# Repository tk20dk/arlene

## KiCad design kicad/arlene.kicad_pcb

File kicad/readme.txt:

0C  = 34.2K 14.6uA
10C = 20.0K 25.0uA
25C = 10.0K 50.0uA
60C =  2.5K 200.0uA

2.8V / 0.0002A = 14K

3.30V at 60C
1.20V at 25C
1.15V at 10C
1.00v at 0C

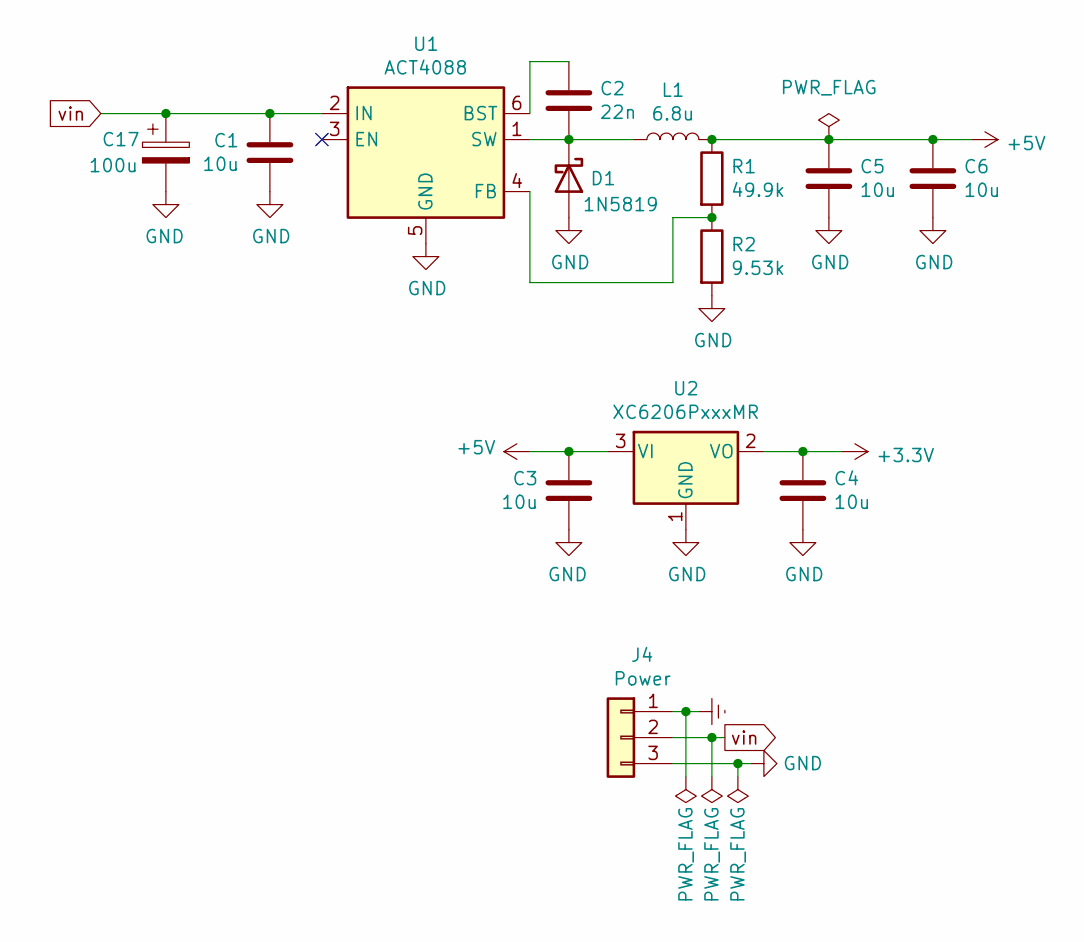
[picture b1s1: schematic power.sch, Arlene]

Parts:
C1, C3, C4, C5, C6: 10u; C_0805_2012Metric
C2: 22n; C_0603_1608Metric
C17: 100u; CP_EIA-7343-31_Kemet-D
D1: 1N5819; D_0805_2012Metric
J4: Power; JST_XH_B3B-XH-A_1x03_P2.50mm_Vertical
L1: 6.8u; L_4.1x4.1_H1.75
R1: 49.9k; R_0603_1608Metric
R2: 9.53k; R_0603_1608Metric
U1: ACT4088; SOT-23-6
U2: XC6206PxxxMR; SOT-23

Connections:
+5V: C3.1, C5.1, C6.1, L1.2, R1.1, U2.3 (VI); also elsewhere on the board
Earth: J4.1; also elsewhere on the board
GND: C1.2, C3.2, C4.2, C5.2, C6.2, C17.2, D1.2 (A), J4.3, R2.2, U1.5 (GND), U2.1 (GND); also elsewhere on the board
unnamed: C2.1, U1.6 (BST)
unnamed: C2.2, D1.1 (K), L1.1, U1.1 (SW)
unnamed: R1.2, R2.1, U1.4 (FB)
vin: C1.1, C17.1, J4.2, U1.2 (IN); also elsewhere on the board

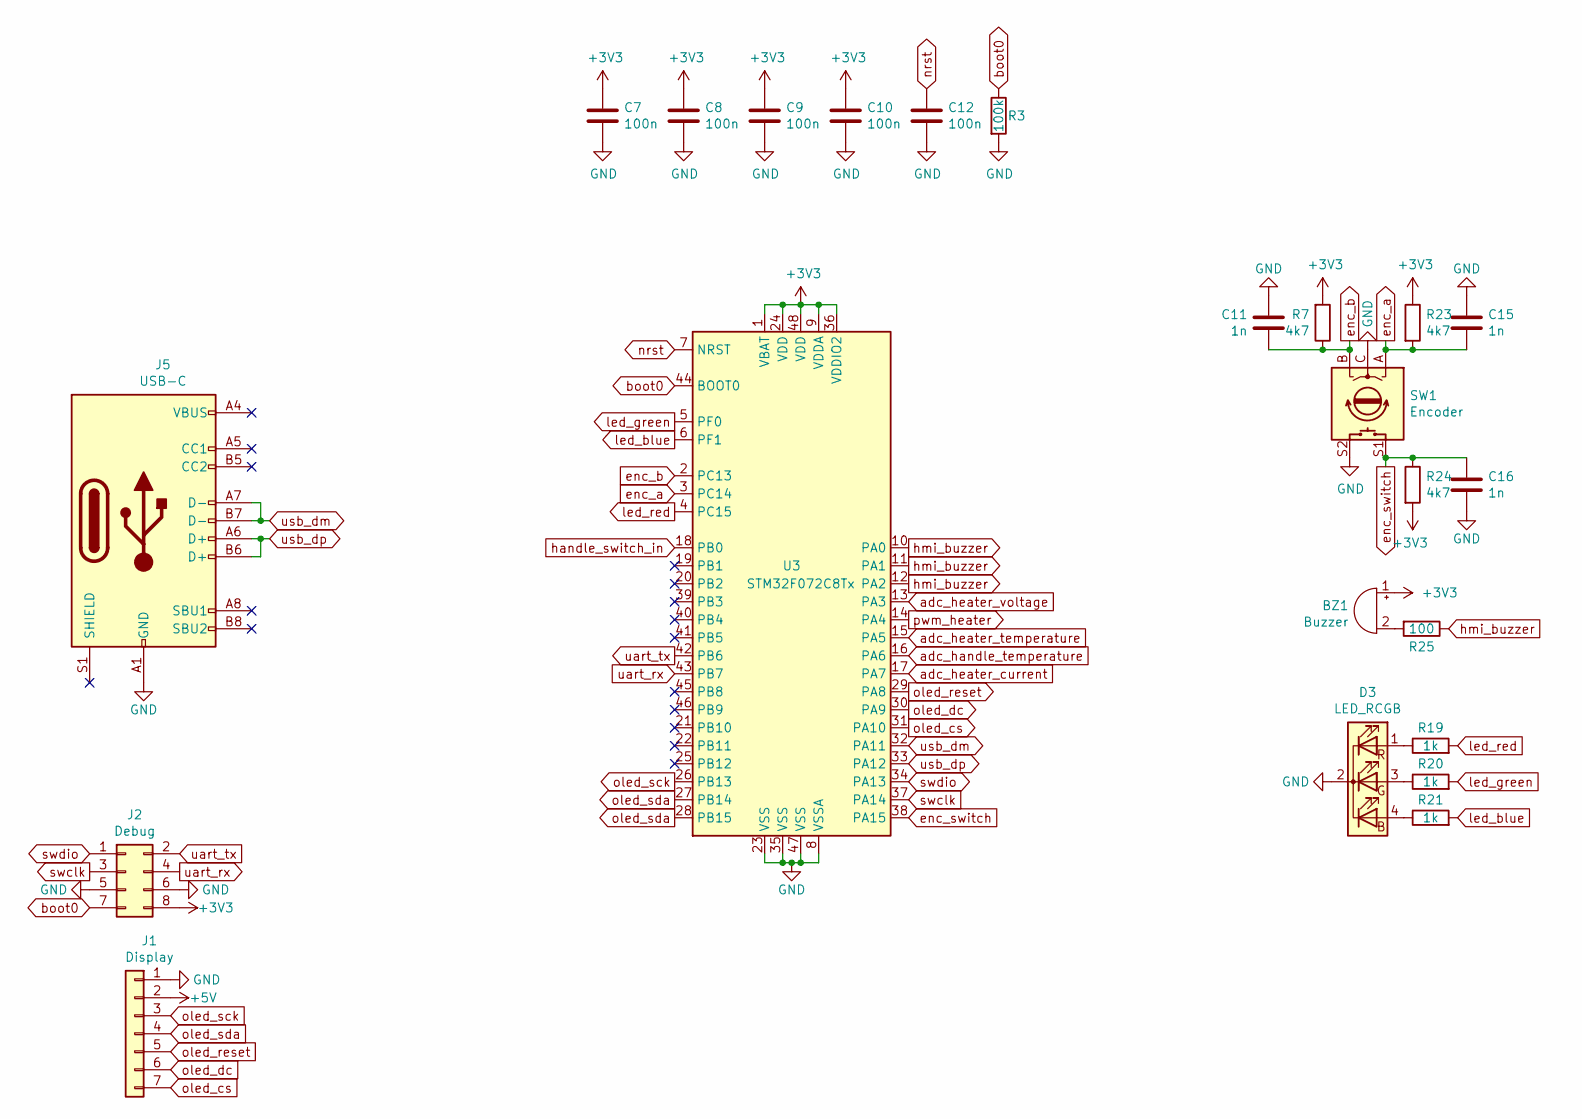
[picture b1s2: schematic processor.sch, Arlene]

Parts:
BZ1: Buzzer; Buzzer_12x9.5RM7.6
C7, C8, C9, C10, C12: 100n; C_0603_1608Metric
C11, C15, C16: 1n; C_0603_1608Metric
D3: LED_RCGB; LED_D5.0mm-4_RGB
J1: Display; PinHeader_1x07_P2.54mm_Vertical
J2: Debug; PinHeader_2x04_P2.54mm_Vertical
J5: USB-C; usb-c_14pin_tht_vertical
R3: 100k; R_0603_1608Metric
R7, R23, R24: 4k7; R_0603_1608Metric
R19, R20, R21: 1k; R_0603_1608Metric
R25: 100; R_0603_1608Metric
SW1: Encoder; RotaryEncoder_Alps_EC12E-Switch_Vertical_H20mm
U3: STM32F072C8Tx; LQFP-48_7x7mm_P0.5mm

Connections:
+5V: J1.2; also elsewhere on the board
GND: C7.2, C8.2, C9.2, C10.2, C11.2, C12.2, C15.1, C16.2, D3.2 (K), J1.1, J2.5, J2.6, J5.A1 (GND), J5.A12 (GND), J5.B1 (GND), J5.B12 (GND), R3.2, SW1.C, SW1.S2, U3.8 (VSSA), U3.23 (VSS), U3.35 (VSS), U3.47 (VSS); also elsewhere on the board
unnamed: BZ1.2 (+), R25.2
unnamed: D3.1 (RA), R19.1
unnamed: D3.3 (GA), R20.1
unnamed: D3.4 (BA), R21.1
unnamed: J5.A4 (VBUS), J5.A9 (VBUS), J5.B4 (VBUS), J5.B9 (VBUS)
adc_handle_temperature: U3.16 (PA6); also elsewhere on the board
adc_heater_current: U3.17 (PA7); also elsewhere on the board
adc_heater_temperature: U3.15 (PA5); also elsewhere on the board
adc_heater_voltage: U3.13 (PA3); also elsewhere on the board
boot0: J2.7, R3.1, U3.44 (BOOT0)
enc_a: C15.2, R23.2, SW1.A, U3.3 (PC14)
enc_b: C11.1, R7.1, SW1.B, U3.2 (PC13)
enc_switch: C16.1, R24.1, SW1.S1, U3.38 (PA15)
handle_switch_in: U3.18 (PB0); also elsewhere on the board
hmi_buzzer: R25.1, U3.10 (PA0), U3.11 (PA1), U3.12 (PA2)
led_blue: R21.2, U3.6 (PF1)
led_green: R20.2, U3.5 (PF0)
led_red: R19.2, U3.4 (PC15)
nrst: C12.1, U3.7 (NRST)
oled_cs: J1.7, U3.31 (PA10)
oled_dc: J1.6, U3.30 (PA9)
oled_reset: J1.5, U3.29 (PA8)
oled_sck: J1.3, U3.26 (PB13)
oled_sda: J1.4, U3.27 (PB14), U3.28 (PB15)
pwm_heater: U3.14 (PA4); also elsewhere on the board
swclk: J2.3, U3.37 (PA14)
swdio: J2.1, U3.34 (PA13)
uart_rx: J2.4, U3.43 (PB7)
uart_tx: J2.2, U3.42 (PB6)
usb_dm: J5.A7 (D-), J5.B7 (D-), U3.32 (PA11)
usb_dp: J5.A6 (D+), J5.B6 (D+), U3.33 (PA12)

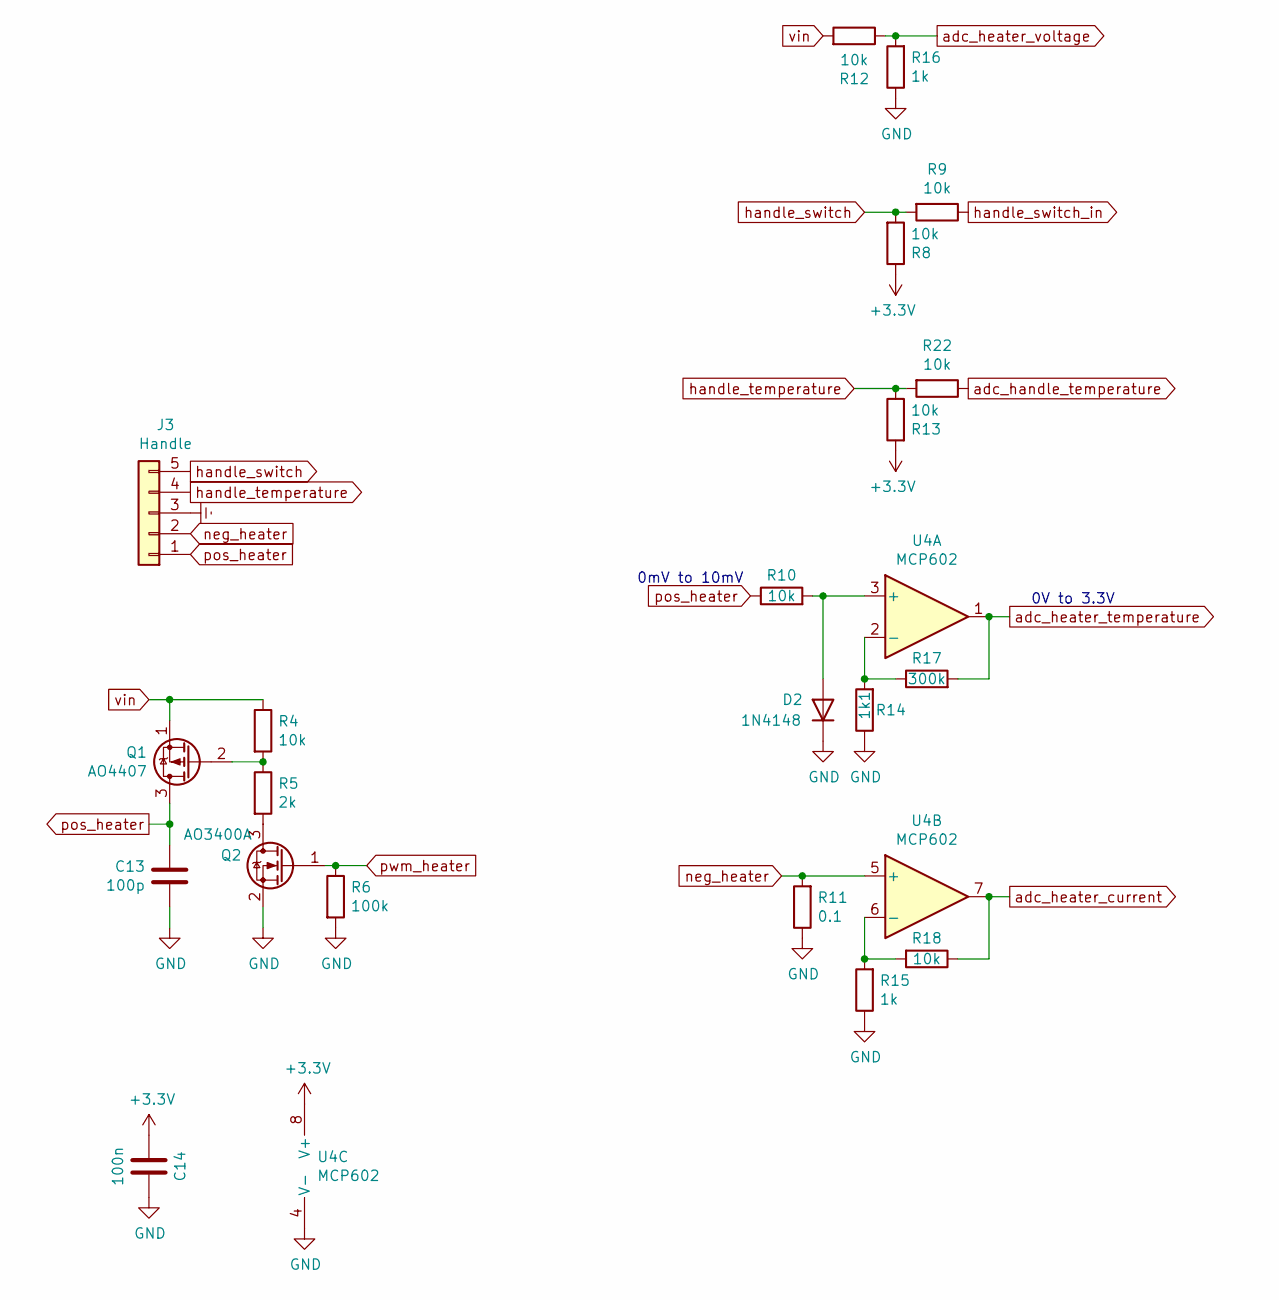
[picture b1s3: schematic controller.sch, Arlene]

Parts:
C13: 100p; C_0603_1608Metric
C14: 100n; C_0603_1608Metric
D2: 1N4148; D_SOD-323
J3: Handle; JST_XH_B5B-XH-A_1x05_P2.50mm_Vertical
Q1: AO4407; SOIC-8_PMOS_SGD_3.9x4.9mm_P1.27mm
Q2: AO3400A; SOT-23
R4, R8, R9, R10, R12, R13, R18, R22: 10k; R_0603_1608Metric
R5: 2k; R_0603_1608Metric
R6: 100k; R_0603_1608Metric
R11: 0.1; R_2512_6332Metric
R14: 1k1; R_0603_1608Metric
R15, R16: 1k; R_0603_1608Metric
R17: 300k; R_0603_1608Metric
U4: MCP602; SOIC-8_3.9x4.9mm_P1.27mm

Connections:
Earth: J3.3; also elsewhere on the board
GND: C13.2, C14.1, D2.1 (K), Q2.2 (S), R6.2, R11.1, R14.1, R15.1, R16.1, U4.4 (V-); also elsewhere on the board
unnamed: D2.2 (A), R10.2, U4.3 (+)
unnamed: Q1.2 (G), R4.2, R5.1
unnamed: Q2.3 (D), R5.2
unnamed: R14.2, R17.1, U4.2 (-)
unnamed: R15.2, R18.2, U4.6 (-)
adc_handle_temperature: R22.1; also elsewhere on the board
adc_heater_current: R18.1, U4.7; also elsewhere on the board
adc_heater_temperature: R17.2, U4.1; also elsewhere on the board
adc_heater_voltage: R12.1, R16.2; also elsewhere on the board
handle_switch: J3.5, R8.2, R9.2
handle_switch_in: R9.1; also elsewhere on the board
handle_temperature: J3.4, R13.1, R22.2
neg_heater: J3.2, R11.2, U4.5 (+)
pos_heater: C13.1, J3.1, Q1.3 (D), R10.1
pwm_heater: Q2.1 (G), R6.1; also elsewhere on the board
vin: Q1.1 (S), R4.1, R12.2; also elsewhere on the board

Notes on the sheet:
0V to 3.3V
0mV to 10mV

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
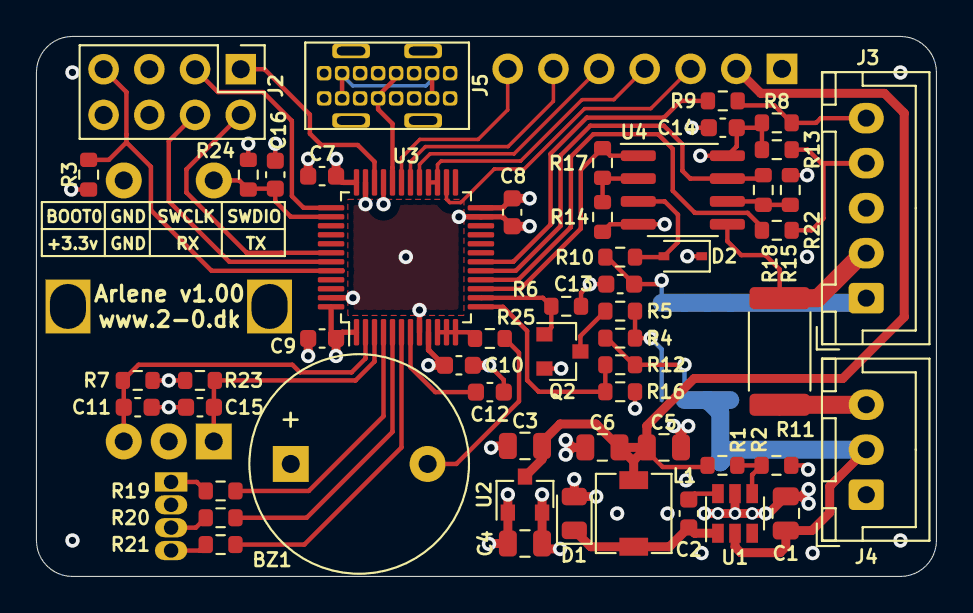
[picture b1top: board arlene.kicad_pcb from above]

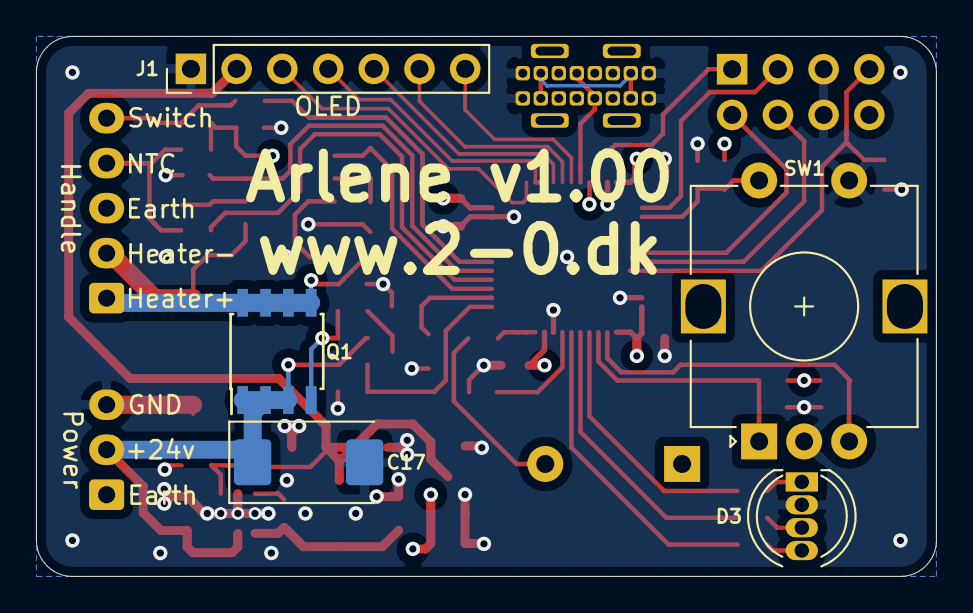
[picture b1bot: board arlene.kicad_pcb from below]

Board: 4 copper layers, 50.0 x 30.0 mm, 59 parts (5 on the bottom side), 48 nets.

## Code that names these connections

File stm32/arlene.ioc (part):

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PB13.GPIOParameters=GPIO_PuPd,GPIO_Label,GPIO_ModeDefaultEXTI
Mcu.UserName=STM32F072C8Tx
PB14.GPIO_Label=LED2_GREEN
PA11.Mode=Device
PA6.GPIO_Label=HMI_BUZZER
PB13.GPIO_Label=ENC_A
PB13.Signal=GPXTI13
PB15.Signal=GPIO_Output
RCC.SYSCLKSource=RCC_SYSCLKSOURCE_HSI48
PA15.GPIO_Label=LED1_RED
PB4.GPIOParameters=GPIO_Label
PA12.Signal=USB_DP
PB6.Signal=I2C1_SCL
PB6.Mode=I2C
PA8.GPIOParameters=GPIO_Label
PA4.GPIO_PuPd=GPIO_PULLUP
PB12.GPIO_Label=ENC_B
PA14.Mode=Serial_Wire
PA0.Mode=IN0
PB3.GPIOParameters=GPIO_Label
PB7.Signal=I2C1_SDA
PA8.Signal=GPIO_Output
PA0.Signal=ADC_IN0
Mcu.Package=LQFP48
PA6.Signal=GPIO_Output
PA10.Signal=USART1_RX
PA15.Signal=GPIO_Output
PA5.GPIOParameters=GPIO_Label
PB14.GPIOParameters=GPIO_Label
PA4.GPIO_Label=HANDLE_SWITCH
PB4.Signal=GPIO_Output
PA3.Signal=ADC_IN3
PB3.GPIO_Label=LED1_GREEN
PA6.GPIOParameters=GPIO_Label
PA15.GPIOParameters=GPIO_Label
PA10.Mode=Asynchronous
PA7.GPIO_ModeDefaultEXTI=GPIO_MODE_IT_FALLING
PB13.GPIO_ModeDefaultEXTI=GPIO_MODE_IT_FALLING
PA13.Signal=SYS_SWDIO
PA3.Mode=IN3
PA9.Mode=Asynchronous
PA8.GPIO_Label=LED2_BLUE
PA9.Signal=USART1_TX
PA4.GPIO_ModeDefaultEXTI=GPIO_MODE_IT_FALLING
PA1.Signal=ADC_IN1
PA7.GPIO_PuPd=GPIO_PULLUP
PB14.Signal=GPIO_Output
PA5.Signal=S_TIM2_CH1_ETR
board=custom
PB13.GPIO_PuPd=GPIO_PULLUP
PA1.Mode=IN1
PB4.GPIO_Label=LED1_BLUE
PB15.GPIO_Label=LED2_RED
PA4.GPIOParameters=GPIO_PuPd,GPIO_Label,GPIO_ModeDefaultEXTI
PB15.GPIOParameters=GPIO_Label
PA13.Mode=Serial_Wire
Mcu.Name=STM32F072C(8-B)Tx
PA2.Signal=ADC_IN2
PB3.Signal=GPIO_Output
PA4.Signal=GPXTI4
RCC.SYSCLKFreq_VALUE=48000000
PA7.GPIO_Label=ENC_SWITCH
PA12.Mode=Device
PA5.GPIO_Label=PWM_HEATER
PA11.Signal=USB_DM
PB7.Mode=I2C
PA14.Signal=SYS_SWCLK
PB12.GPIO_ModeDefaultEXTI=GPIO_MODE_IT_FALLING
PA2.Mode=IN2
PB12.GPIO_PuPd=GPIO_PULLUP
PA7.GPIOParameters=GPIO_PuPd,GPIO_Label,GPIO_ModeDefaultEXTI
PB12.GPIOParameters=GPIO_PuPd,GPIO_Label,GPIO_ModeDefaultEXTI
PB12.Signal=GPXTI12
PA7.Signal=GPXTI7

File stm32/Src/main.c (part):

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  __HAL_RCC_GPIOB_CLK_ENABLE();

  /*Configure GPIO pin Output Level */
  HAL_GPIO_WritePin(GPIOA, HMI_BUZZER_Pin|LED2_BLUE_Pin|LED1_RED_Pin, GPIO_PIN_RESET);

  /*Configure GPIO pin Output Level */
  HAL_GPIO_WritePin(GPIOB, LED2_GREEN_Pin|LED2_RED_Pin|LED1_GREEN_Pin|LED1_BLUE_Pin, GPIO_PIN_RESET);

  /*Configure GPIO pins : PC13 PC14 PC15 */
  GPIO_InitStruct.Pin = GPIO_PIN_13|GPIO_PIN_14|GPIO_PIN_15;
  GPIO_InitStruct.Mode = GPIO_MODE_ANALOG;
  GPIO_InitStruct.Pull = GPIO_NOPULL;
  HAL_GPIO_Init(GPIOC, &GPIO_InitStruct);

  /*Configure GPIO pins : PF0 PF1 */
  GPIO_InitStruct.Pin = GPIO_PIN_0|GPIO_PIN_1;
  GPIO_InitStruct.Mode = GPIO_MODE_ANALOG;
  GPIO_InitStruct.Pull = GPIO_NOPULL;
  HAL_GPIO_Init(GPIOF, &GPIO_InitStruct);

  /*Configure GPIO pins : HANDLE_SWITCH_Pin ENC_SWITCH_Pin */
  GPIO_InitStruct.Pin = HANDLE_SWITCH_Pin|ENC_SWITCH_Pin;
  GPIO_InitStruct.Mode = GPIO_MODE_IT_FALLING;
  GPIO_InitStruct.Pull = GPIO_PULLUP;
  HAL_GPIO_Init(GPIOA, &GPIO_InitStruct);

  /*Configure GPIO pins : HMI_BUZZER_Pin LED2_BLUE_Pin LED1_RED_Pin */
  GPIO_InitStruct.Pin = HMI_BUZZER_Pin|LED2_BLUE_Pin|LED1_RED_Pin;
  GPIO_InitStruct.Mode = GPIO_MODE_OUTPUT_PP;
  GPIO_InitStruct.Pull = GPIO_NOPULL;
  GPIO_InitStruct.Speed = GPIO_SPEED_FREQ_LOW;
  HAL_GPIO_Init(GPIOA, &GPIO_InitStruct);

  /*Configure GPIO pins : PB0 PB1 PB2 PB10 
                           PB11 PB5 PB8 PB9 */
  GPIO_InitStruct.Pin = GPIO_PIN_0|GPIO_PIN_1|GPIO_PIN_2|GPIO_PIN_10 
                          |GPIO_PIN_11|GPIO_PIN_5|GPIO_PIN_8|GPIO_PIN_9;
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  GPIO_InitStruct.Pull = GPIO_NOPULL;
  HAL_GPIO_Init(GPIOB, &GPIO_InitStruct);

  /*Configure GPIO pins : ENC_B_Pin ENC_A_Pin */
  GPIO_InitStruct.Pin = ENC_B_Pin|ENC_A_Pin;
  GPIO_InitStruct.Mode = GPIO_MODE_IT_FALLING;
  GPIO_InitStruct.Pull = GPIO_PULLUP;
  HAL_GPIO_Init(GPIOB, &GPIO_InitStruct);
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
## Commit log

2020-11-20 created initial kicad and stm32 and stm32 projects
2021-07-29 updated project to STM32CubeIDE 1.6.1
2021-07-29 updated project to STM32CudeIDE 1.6.1
2021-08-01 updated controller
2021-08-05 Arlene v1.00
2021-08-06 JLCPCB exit!

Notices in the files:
stm32/Src/main.c:
© Copyright (c) 2019 STMicroelectronics.
All rights reserved.
This software component is licensed by ST under Ultimate Liberty license
(C) COPYRIGHT STMicroelectronics *****END OF FILE
